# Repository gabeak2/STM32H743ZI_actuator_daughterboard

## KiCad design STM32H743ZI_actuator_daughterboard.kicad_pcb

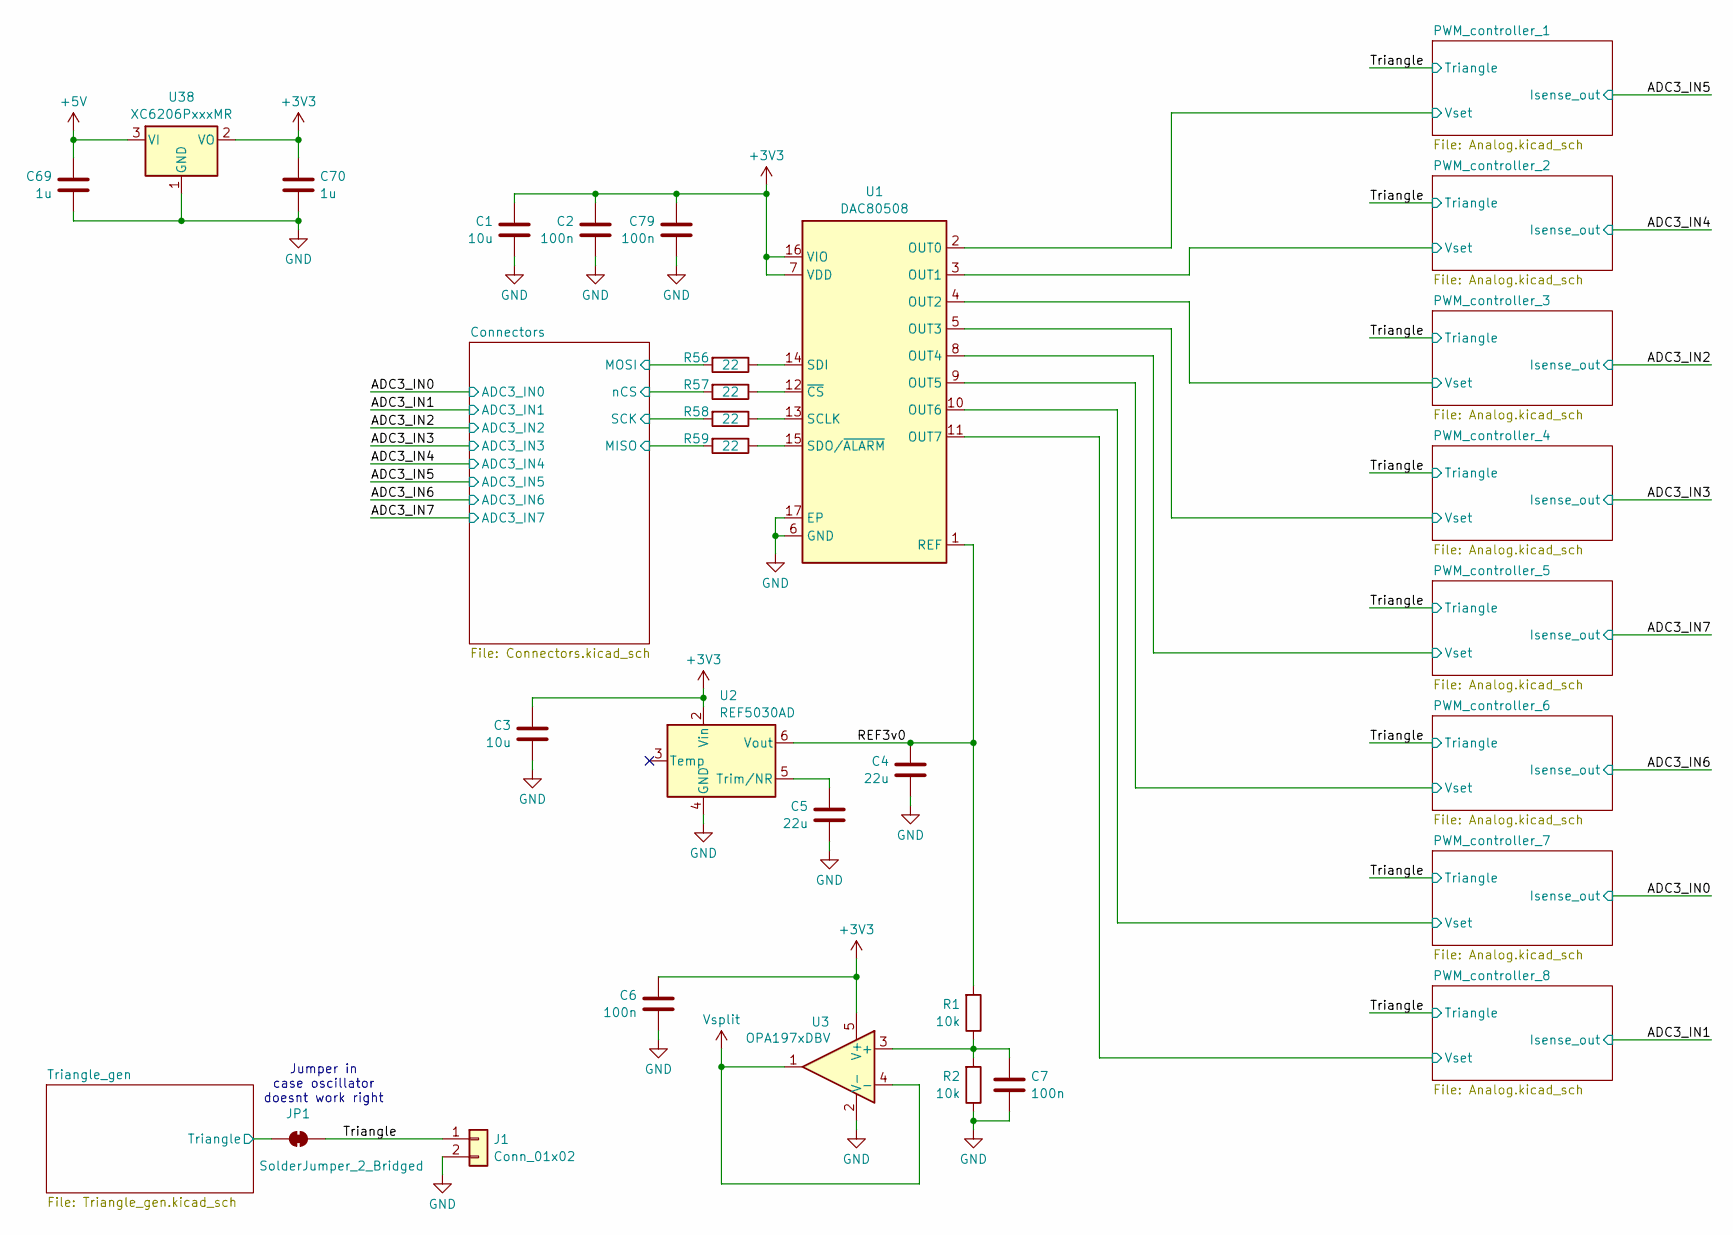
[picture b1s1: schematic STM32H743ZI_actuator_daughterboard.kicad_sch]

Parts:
C1, C3: 10u; C_0603_1608Metric; LCSC C19702
C2, C6, C7, C79: 100n; C_0603_1608Metric; LCSC C14663
C4, C5: 22u; C_0603_1608Metric; LCSC C59461
C69, C70: 1u; C_0603_1608Metric; LCSC C52923
J1: Conn_01x02; PinHeader_1x02_P2.54mm_Vertical
JP1: SolderJumper_2_Bridged; SolderJumper-2_P1.3mm_Bridged2Bar_Pad1.0x1.5mm
R1, R2: 10k; R_0603_1608Metric; LCSC C25804
R56, R57, R58, R59: 22; R_0603_1608Metric; LCSC C23345
U1: DAC80508; Texas_RTE0016D_WQFN-16-1EP_3x3mm_P0.5mm_EP0.8x0.8mm_Thermal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; LCSC C2679499
U2: REF5030AD; SOIC-8_3.9x4.9mm_P1.27mm; LCSC C69362
U3: OPA197xDBV; SOT-23-5; LCSC C221351
U38: XC6206PxxxMR; SOT-23-3; LCSC C5446

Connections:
+3V3: C1.1, C2.1, C3.1, C6.1, C70.1, C79.1, U1.7 (VDD), U1.16 (VIO), U2.2 (Vin), U3.5 (V+), U38.2 (VO); also elsewhere on the board
+5V: C69.1, U38.3 (VI); also elsewhere on the board
/Connectors/SPI1_MISO: R59.2; also elsewhere on the board
/Connectors/SPI1_MOSI: R56.2; also elsewhere on the board
/Connectors/SPI1_SCK: R58.2; also elsewhere on the board
/Connectors/SPI1_nCS: R57.2; also elsewhere on the board
/PWM_controller_1/Vset: U1.2 (OUT0); also elsewhere on the board
/PWM_controller_2/Vset: U1.3 (OUT1); also elsewhere on the board
/PWM_controller_3/Vset: U1.4 (OUT2); also elsewhere on the board
/PWM_controller_4/Vset: U1.5 (OUT3); also elsewhere on the board
/PWM_controller_5/Vset: U1.8 (OUT4); also elsewhere on the board
/PWM_controller_6/Vset: U1.9 (OUT5); also elsewhere on the board
/PWM_controller_7/Vset: U1.10 (OUT6); also elsewhere on the board
/PWM_controller_8/Vset: U1.11 (OUT7); also elsewhere on the board
/REF3v0: C4.1, R1.2, U1.1 (REF), U2.6 (Vout)
/Triangle: J1.1, JP1.1 (A); also elsewhere on the board
/Triangle_gen/Triangle: JP1.2 (B); also elsewhere on the board
GND: C1.2, C2.2, C3.2, C4.2, C5.2, C6.2, C7.2, C69.2, C70.2, C79.2, J1.2, R2.1, U1.6 (GND), U1.17 (EP), U2.4 (GND), U3.2 (V-), U38.1 (GND); also elsewhere on the board
unnamed: R58.1, U1.13 (SCLK)
unnamed: R56.1, U1.14 (SDI)
unnamed: R59.1, U1.15 (SDO/~ALARM)
unnamed: R57.1, U1.12 (~CS)
unnamed: C5.1, U2.5 (Trim/NR)
unnamed: C7.1, R1.1, R2.2, U3.3 (+)
Vsplit: U3.1, U3.4 (-); also elsewhere on the board

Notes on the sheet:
Jumper in case oscillator doesnt work right

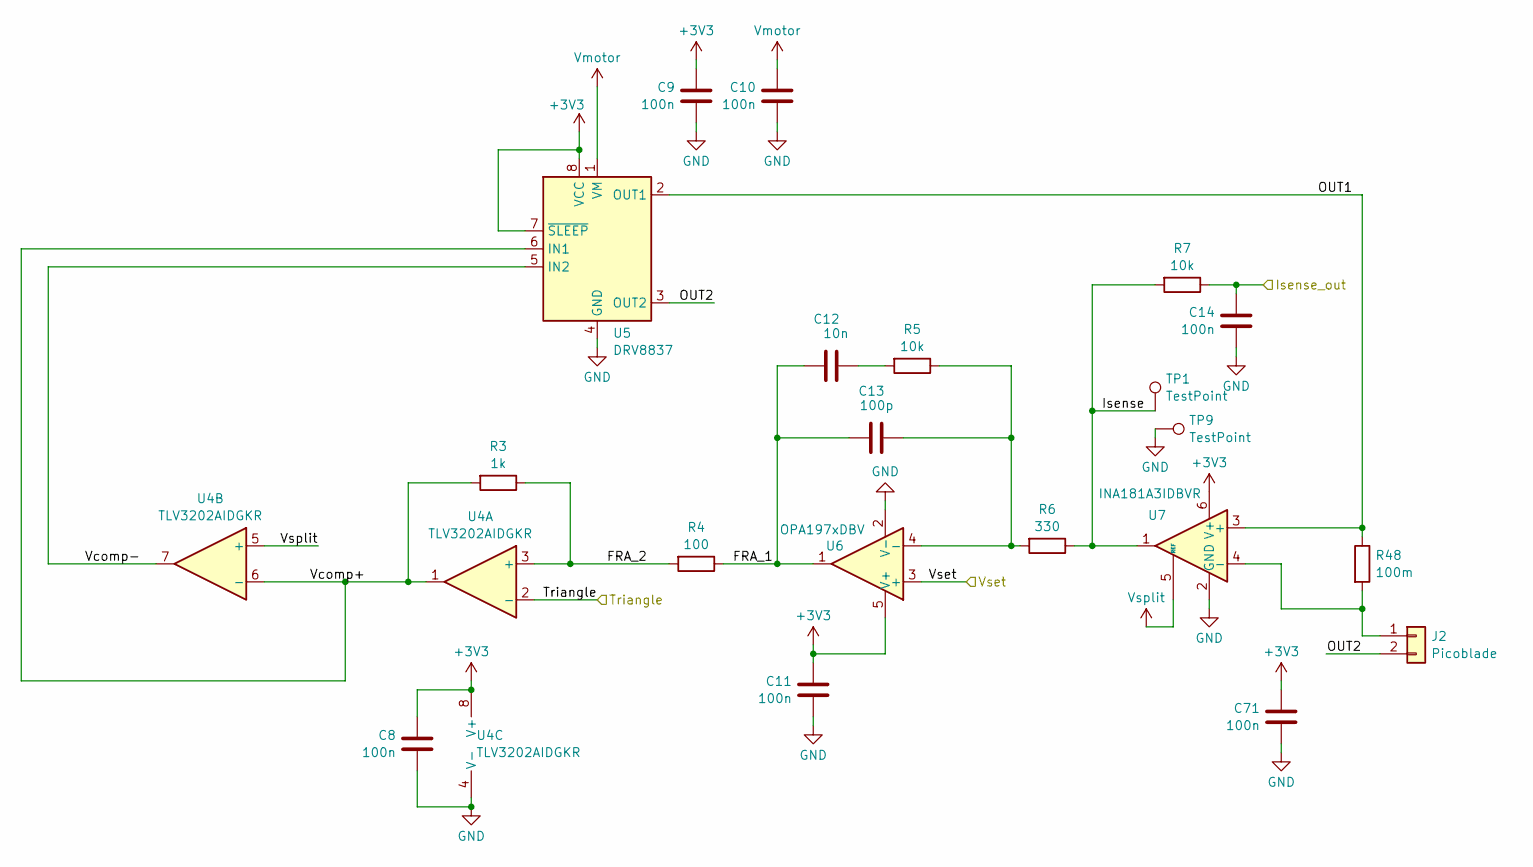
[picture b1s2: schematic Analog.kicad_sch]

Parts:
C8, C9, C10, C11, C14, C71: 100n; C_0603_1608Metric; LCSC C14663
C12: 10n; C_0603_1608Metric; LCSC C57112
C13: 100p; C_0603_1608Metric; LCSC C14858
J2: Picoblade; Molex_PicoBlade_53047-0210_1x02_P1.25mm_Vertical
R3: 1k; R_0603_1608Metric; LCSC C21190
R4: 100; R_0603_1608Metric; LCSC C22775
R5, R7: 10k; R_0603_1608Metric; LCSC C25804
R6: 330; R_0603_1608Metric; LCSC C23138
R48: 100m; R_1206_3216Metric; LCSC C25334
TP1, TP9: TestPoint; scope_tp
U4: TLV3202AIDGKR; VSSOP-8_3x3mm_P0.65mm; LCSC C478075
U5: DRV8837; WSON-8-1EP_2x2mm_P0.5mm_EP0.9x1.6mm; LCSC C39159
U6: OPA197xDBV; SOT-23-5; LCSC C221351
U7: INA181A3IDBVR; SOT-23-6; LCSC C2652255

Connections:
+3V3: C8.1, C9.1, C11.1, C71.1, U4.8 (V+), U5.7 (~SLEEP), U5.8 (VCC), U6.5 (V+), U7.6 (V+); also elsewhere on the board
/ADC3_IN5: C14.1, R7.1; also elsewhere on the board
/PWM_controller_1/FRA_1: C12.1, C13.1, R4.1, U6.1
/PWM_controller_1/FRA_2: R3.1, R4.2, U4.3 (+)
/PWM_controller_1/Isense: R6.1, R7.2, TP1.1 (1_1), U7.1
/PWM_controller_1/OUT1: R48.1, U5.2 (OUT1), U7.3 (+)
/PWM_controller_1/OUT2: J2.2, U5.3 (OUT2)
/PWM_controller_1/Vcomp+: R3.2, U4.1, U4.6 (-), U5.6 (IN1)
/PWM_controller_1/Vcomp-: U4.7, U5.5 (IN2)
/PWM_controller_1/Vset: U6.3 (+); also elsewhere on the board
/Triangle: U4.2 (-); also elsewhere on the board
GND: C8.2, C9.2, C10.2, C11.2, C14.2, C71.2, TP9.1 (1_1), U4.4 (V-), U5.4 (GND), U5.9 (GND), U6.2 (V-), U7.2 (GND); also elsewhere on the board
unnamed: C12.2, R5.2
unnamed: J2.1, R48.2, U7.4 (-)
unnamed: C13.2, R5.1, R6.2, U6.4 (-)
Vmotor: C10.1, U5.1 (VM); also elsewhere on the board
Vsplit: U4.5 (+), U7.5 (REF); also elsewhere on the board

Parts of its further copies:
C15, C16, C19, C20, C21, C22, C23, C26, C27, C28, C29, C30, C33, C34, C35, C36, C37, C40, C41, C42, C43, C44, C47, C48, C49, C50, C51, C54, C55, C56, C57, C58, C61, C62, C63, C72, C73, C74, C75, C76, C77, C78: 100n; C_0603_1608Metric; LCSC C14663
C17, C24, C31, C38, C45, C52, C59: 10n; C_0603_1608Metric; LCSC C57112
C18, C25, C32, C39, C46, C53, C60: 100p; C_0603_1608Metric; LCSC C14858
J5, J7, J9, J11, J13, J15, J17: Picoblade; Molex_PicoBlade_53047-0210_1x02_P1.25mm_Vertical
R8, R13, R18, R23, R28, R33, R38, R49, R50, R51, R52, R53, R54, R55: 10k; R_0603_1608Metric; LCSC C25804
R9, R14, R19, R24, R29, R34, R39: 1k; R_0603_1608Metric; LCSC C21190
R10, R15, R20, R25, R30, R35, R40: 330; R_0603_1608Metric; LCSC C23138
R11, R16, R21, R26, R31, R36, R41: 100; R_0603_1608Metric; LCSC C22775
R12, R17, R22, R27, R32, R37, R42: 100m; R_1206_3216Metric; LCSC C25334
TP2, TP3, TP4, TP5, TP6, TP7, TP8, TP10, TP11, TP12, TP13, TP14, TP15, TP16: TestPoint; scope_tp
U8, U12, U16, U20, U24, U28, U32: DRV8837; WSON-8-1EP_2x2mm_P0.5mm_EP0.9x1.6mm; LCSC C39159
U9, U13, U17, U21, U25, U29, U33: INA181A3IDBVR; SOT-23-6; LCSC C2652255
U10, U14, U18, U22, U26, U30, U34: TLV3202AIDGKR; VSSOP-8_3x3mm_P0.65mm; LCSC C478075
U11, U15, U19, U23, U27, U31, U35: OPA197xDBV; SOT-23-5; LCSC C221351

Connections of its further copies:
+3V3: C15.1, C19.1, C20.1, C21.1, C22.1, C26.1, C27.1, C28.1, C29.1, C33.1, C34.1, C35.1, C36.1, C40.1, C41.1, C42.1, C43.1, C47.1, C48.1, C49.1, C50.1, C54.1, C55.1, C56.1, C57.1, C61.1, C62.1, C63.1, U8.7 (~SLEEP), U8.8 (VCC), U9.6 (V+), U10.8 (V+), U11.5 (V+), U12.7 (~SLEEP), U12.8 (VCC), U13.6 (V+), U14.8 (V+), U15.5 (V+), U16.7 (~SLEEP), U16.8 (VCC), U17.6 (V+), U18.8 (V+), U19.5 (V+), U20.7 (~SLEEP), U20.8 (VCC), U21.6 (V+), U22.8 (V+), U23.5 (V+), U24.7 (~SLEEP), U24.8 (VCC), U25.6 (V+), U26.8 (V+), U27.5 (V+), U28.7 (~SLEEP), U28.8 (VCC), U29.6 (V+), U30.8 (V+), U31.5 (V+), U32.7 (~SLEEP), U32.8 (VCC), U33.6 (V+), U34.8 (V+), U35.5 (V+); also elsewhere on the board
/ADC3_IN0: C77.1, R54.1; also elsewhere on the board
/ADC3_IN1: C78.1, R55.1; also elsewhere on the board
/ADC3_IN2: C73.1, R50.1; also elsewhere on the board
/ADC3_IN3: C74.1, R51.1; also elsewhere on the board
/ADC3_IN4: C72.1, R49.1; also elsewhere on the board
/ADC3_IN6: C76.1, R53.1; also elsewhere on the board
/ADC3_IN7: C75.1, R52.1; also elsewhere on the board
/PWM_controller_2/FRA_1: C17.1, C18.1, R11.1, U11.1
/PWM_controller_2/FRA_2: R9.1, R11.2, U10.3 (+)
/PWM_controller_2/Isense: R10.1, R49.2, TP2.1 (1_1), U9.1
/PWM_controller_2/OUT1: R12.1, U8.2 (OUT1), U9.3 (+)
/PWM_controller_2/OUT2: J5.2, U8.3 (OUT2)
/PWM_controller_2/Vcomp+: R9.2, U8.6 (IN1), U10.1, U10.6 (-)
/PWM_controller_2/Vcomp-: U8.5 (IN2), U10.7
/PWM_controller_2/Vset: U11.3 (+); also elsewhere on the board
/PWM_controller_3/FRA_1: C24.1, C25.1, R16.1, U15.1
/PWM_controller_3/FRA_2: R14.1, R16.2, U14.3 (+)
/PWM_controller_3/Isense: R15.1, R50.2, TP3.1 (1_1), U13.1
/PWM_controller_3/OUT1: R17.1, U12.2 (OUT1), U13.3 (+)
/PWM_controller_3/OUT2: J7.2, U12.3 (OUT2)
/PWM_controller_3/Vcomp+: R14.2, U12.6 (IN1), U14.1, U14.6 (-)
/PWM_controller_3/Vcomp-: U12.5 (IN2), U14.7
/PWM_controller_3/Vset: U15.3 (+); also elsewhere on the board
/PWM_controller_4/FRA_1: C31.1, C32.1, R21.1, U19.1
/PWM_controller_4/FRA_2: R19.1, R21.2, U18.3 (+)
/PWM_controller_4/Isense: R20.1, R51.2, TP4.1 (1_1), U17.1
/PWM_controller_4/OUT1: R22.1, U16.2 (OUT1), U17.3 (+)
/PWM_controller_4/OUT2: J9.2, U16.3 (OUT2)
/PWM_controller_4/Vcomp+: R19.2, U16.6 (IN1), U18.1, U18.6 (-)
/PWM_controller_4/Vcomp-: U16.5 (IN2), U18.7
/PWM_controller_4/Vset: U19.3 (+); also elsewhere on the board
/PWM_controller_5/FRA_1: C38.1, C39.1, R26.1, U23.1
/PWM_controller_5/FRA_2: R24.1, R26.2, U22.3 (+)
/PWM_controller_5/Isense: R25.1, R52.2, TP5.1 (1_1), U21.1
/PWM_controller_5/OUT1: R27.1, U20.2 (OUT1), U21.3 (+)
/PWM_controller_5/OUT2: J11.2, U20.3 (OUT2)
/PWM_controller_5/Vcomp+: R24.2, U20.6 (IN1), U22.1, U22.6 (-)
/PWM_controller_5/Vcomp-: U20.5 (IN2), U22.7
/PWM_controller_5/Vset: U23.3 (+); also elsewhere on the board
/PWM_controller_6/FRA_1: C45.1, C46.1, R31.1, U27.1
/PWM_controller_6/FRA_2: R29.1, R31.2, U26.3 (+)
/PWM_controller_6/Isense: R30.1, R53.2, TP6.1 (1_1), U25.1
/PWM_controller_6/OUT1: R32.1, U24.2 (OUT1), U25.3 (+)
/PWM_controller_6/OUT2: J13.2, U24.3 (OUT2)
/PWM_controller_6/Vcomp+: R29.2, U24.6 (IN1), U26.1, U26.6 (-)
/PWM_controller_6/Vcomp-: U24.5 (IN2), U26.7
/PWM_controller_6/Vset: U27.3 (+); also elsewhere on the board
/PWM_controller_7/FRA_1: C52.1, C53.1, R36.1, U31.1
/PWM_controller_7/FRA_2: R34.1, R36.2, U30.3 (+)
/PWM_controller_7/Isense: R35.1, R54.2, TP7.1 (1_1), U29.1
/PWM_controller_7/OUT1: R37.1, U28.2 (OUT1), U29.3 (+)
/PWM_controller_7/OUT2: J15.2, U28.3 (OUT2)
/PWM_controller_7/Vcomp+: R34.2, U28.6 (IN1), U30.1, U30.6 (-)
/PWM_controller_7/Vcomp-: U28.5 (IN2), U30.7
/PWM_controller_7/Vset: U31.3 (+); also elsewhere on the board
/PWM_controller_8/FRA_1: C59.1, C60.1, R41.1, U35.1
/PWM_controller_8/FRA_2: R39.1, R41.2, U34.3 (+)
/PWM_controller_8/Isense: R40.1, R55.2, TP8.1 (1_1), U33.1
/PWM_controller_8/OUT1: R42.1, U32.2 (OUT1), U33.3 (+)
/PWM_controller_8/OUT2: J17.2, U32.3 (OUT2)
/PWM_controller_8/Vcomp+: R39.2, U32.6 (IN1), U34.1, U34.6 (-)
/PWM_controller_8/Vcomp-: U32.5 (IN2), U34.7
/PWM_controller_8/Vset: U35.3 (+); also elsewhere on the board
/Triangle: U10.2 (-), U14.2 (-), U18.2 (-), U22.2 (-), U26.2 (-), U30.2 (-), U34.2 (-); also elsewhere on the board
GND: C15.2, C16.2, C19.2, C20.2, C21.2, C22.2, C23.2, C26.2, C27.2, C28.2, C29.2, C30.2, C33.2, C34.2, C35.2, C36.2, C37.2, C40.2, C41.2, C42.2, C43.2, C44.2, C47.2, C48.2, C49.2, C50.2, C51.2, C54.2, C55.2, C56.2, C57.2, C58.2, C61.2, C62.2, C63.2, C72.2, C73.2, C74.2, C75.2, C76.2, C77.2, C78.2, TP10.1 (1_1), TP11.1 (1_1), TP12.1 (1_1), TP13.1 (1_1), TP14.1 (1_1), TP15.1 (1_1), TP16.1 (1_1), U8.4 (GND), U8.9 (GND), U9.2 (GND), U10.4 (V-), U11.2 (V-), U12.4 (GND), U12.9 (GND), U13.2 (GND), U14.4 (V-), U15.2 (V-), U16.4 (GND), U16.9 (GND), U17.2 (GND), U18.4 (V-), U19.2 (V-), U20.4 (GND), U20.9 (GND), U21.2 (GND), U22.4 (V-), U23.2 (V-), U24.4 (GND), U24.9 (GND), U25.2 (GND), U26.4 (V-), U27.2 (V-), U28.4 (GND), U28.9 (GND), U29.2 (GND), U30.4 (V-), U31.2 (V-), U32.4 (GND), U32.9 (GND), U33.2 (GND), U34.4 (V-), U35.2 (V-); also elsewhere on the board
unnamed: C17.2, R8.2
unnamed: C24.2, R13.2
unnamed: C31.2, R18.2
unnamed: C38.2, R23.2
unnamed: C45.2, R28.2
unnamed: C52.2, R33.2
unnamed: C59.2, R38.2
unnamed: J5.1, R12.2, U9.4 (-)
unnamed: J7.1, R17.2, U13.4 (-)
unnamed: J9.1, R22.2, U17.4 (-)
unnamed: J11.1, R27.2, U21.4 (-)
unnamed: J13.1, R32.2, U25.4 (-)
unnamed: J15.1, R37.2, U29.4 (-)
unnamed: J17.1, R42.2, U33.4 (-)
unnamed: C18.2, R8.1, R10.2, U11.4 (-)
unnamed: C25.2, R13.1, R15.2, U15.4 (-)
unnamed: C32.2, R18.1, R20.2, U19.4 (-)
unnamed: C39.2, R23.1, R25.2, U23.4 (-)
unnamed: C46.2, R28.1, R30.2, U27.4 (-)
unnamed: C53.2, R33.1, R35.2, U31.4 (-)
unnamed: C60.2, R38.1, R40.2, U35.4 (-)
Vmotor: C16.1, C23.1, C30.1, C37.1, C44.1, C51.1, C58.1, U8.1 (VM), U12.1 (VM), U16.1 (VM), U20.1 (VM), U24.1 (VM), U28.1 (VM), U32.1 (VM); also elsewhere on the board
Vsplit: U9.5 (REF), U10.5 (+), U13.5 (REF), U14.5 (+), U17.5 (REF), U18.5 (+), U21.5 (REF), U22.5 (+), U25.5 (REF), U26.5 (+), U29.5 (REF), U30.5 (+), U33.5 (REF), U34.5 (+); also elsewhere on the board

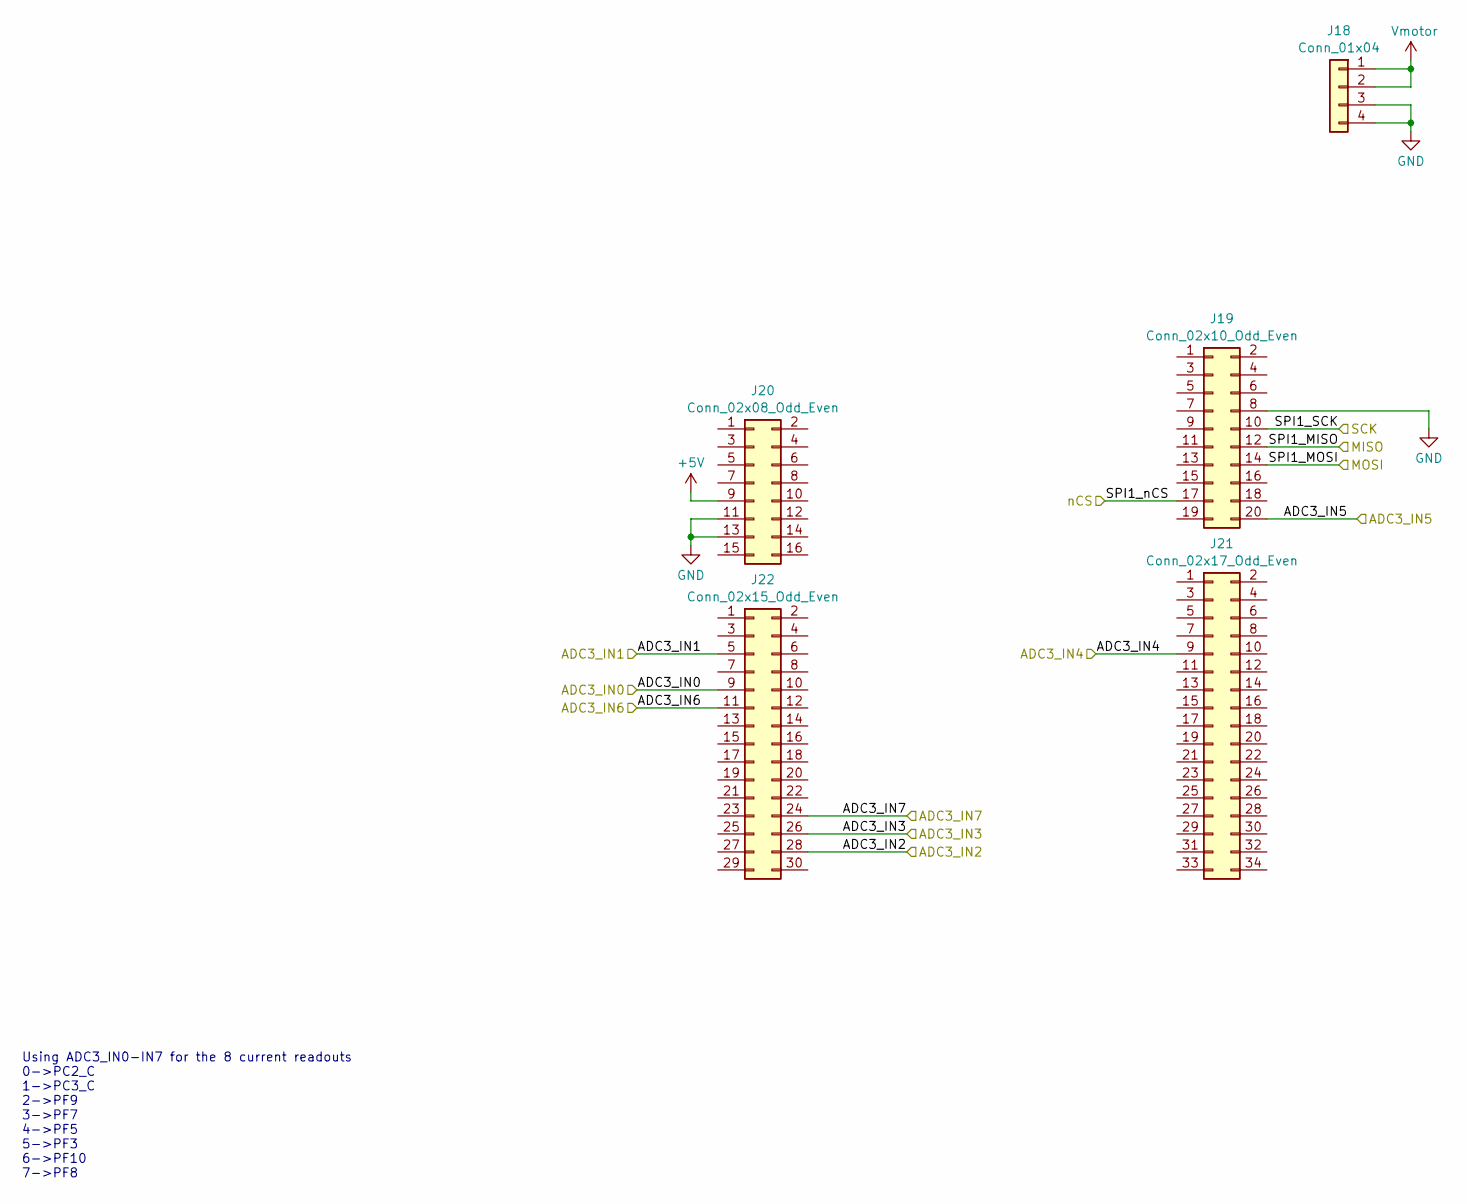
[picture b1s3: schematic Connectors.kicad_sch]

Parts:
J18: Conn_01x04; PinHeader_1x04_P2.54mm_Vertical
J19: Conn_02x10_Odd_Even; PinHeader_2x10_P2.54mm_Vertical
J20: Conn_02x08_Odd_Even; PinHeader_2x08_P2.54mm_Vertical
J21: Conn_02x17_Odd_Even; PinHeader_2x17_P2.54mm_Vertical
J22: Conn_02x15_Odd_Even; PinHeader_2x15_P2.54mm_Vertical

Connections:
+5V: J20.9; also elsewhere on the board
/ADC3_IN0: J22.9; also elsewhere on the board
/ADC3_IN1: J22.5; also elsewhere on the board
/ADC3_IN2: J22.28; also elsewhere on the board
/ADC3_IN3: J22.26; also elsewhere on the board
/ADC3_IN4: J21.9 (Pin_9_9); also elsewhere on the board
/ADC3_IN5: J19.20; also elsewhere on the board
/ADC3_IN6: J22.11; also elsewhere on the board
/ADC3_IN7: J22.24; also elsewhere on the board
/Connectors/SPI1_MISO: J19.12; also elsewhere on the board
/Connectors/SPI1_MOSI: J19.14; also elsewhere on the board
/Connectors/SPI1_SCK: J19.10; also elsewhere on the board
/Connectors/SPI1_nCS: J19.17; also elsewhere on the board
GND: J18.3, J18.4, J19.8, J20.11, J20.13; also elsewhere on the board
Vmotor: J18.1, J18.2; also elsewhere on the board

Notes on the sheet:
Using ADC3_IN0-IN7 for the 8 current readouts 0->PC2_C 1->PC3_C 2->PF9 3->PF7 4->PF5 5->PF3 6->PF10 7->PF8

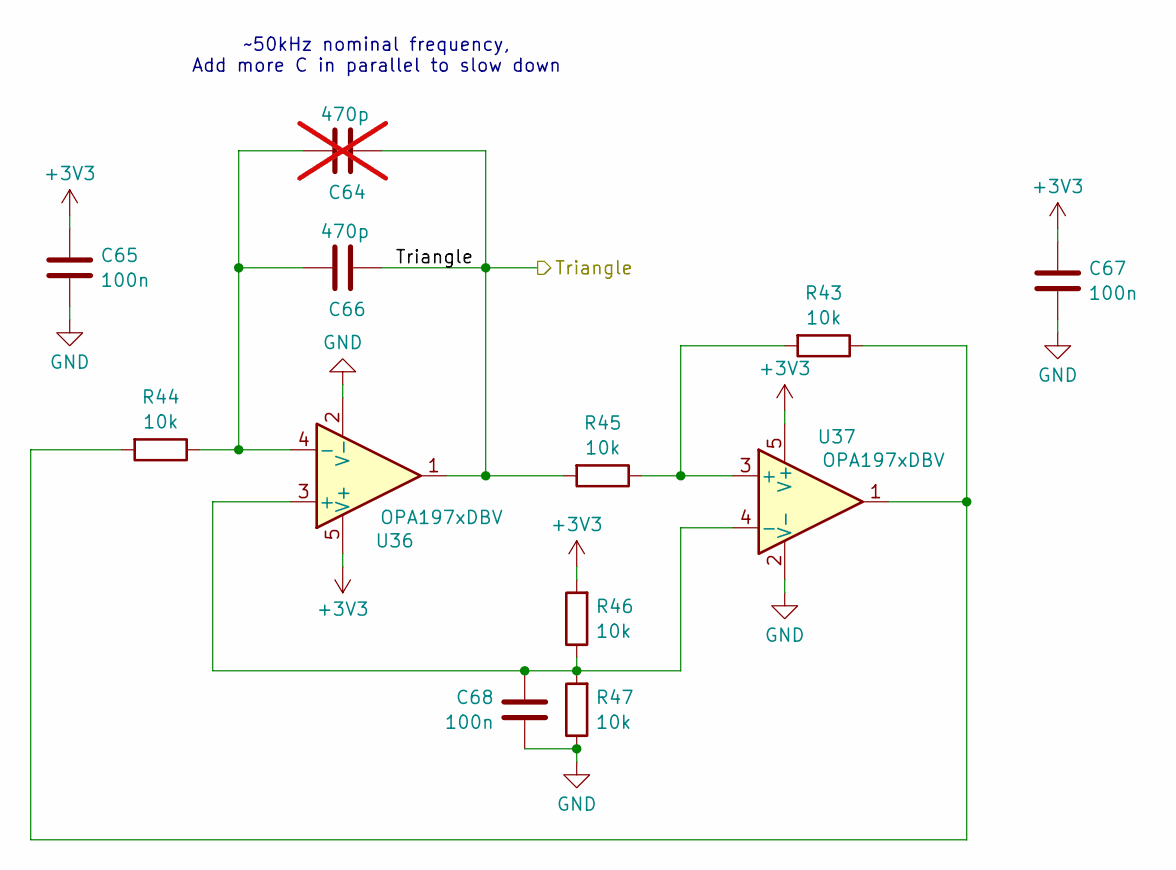
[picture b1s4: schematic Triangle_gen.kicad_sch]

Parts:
C64: 470p; C_0603_1608Metric; LCSC C1620; not fitted
C65, C67, C68: 100n; C_0603_1608Metric; LCSC C14663
C66: 470p; C_0603_1608Metric; LCSC C1620
R43, R44, R45, R46, R47: 10k; R_0603_1608Metric; LCSC C25804
U36, U37: OPA197xDBV; SOT-23-5; LCSC C221351

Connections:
+3V3: C65.1, C67.1, R46.2, U36.5 (V+), U37.5 (V+); also elsewhere on the board
/Triangle_gen/Triangle: C64.1, C66.1, R45.2, U36.1; also elsewhere on the board
GND: C65.2, C67.2, C68.2, R47.1, U36.2 (V-), U37.2 (V-); also elsewhere on the board
unnamed: R43.1, R44.2, U37.1
unnamed: C68.1, R46.1, R47.2, U36.3 (+), U37.4 (-)
unnamed: C64.2, C66.2, R44.1, U36.4 (-)
unnamed: R43.2, R45.1, U37.3 (+)

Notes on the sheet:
~50kHz nominal frequency, Add more C in parallel to slow down

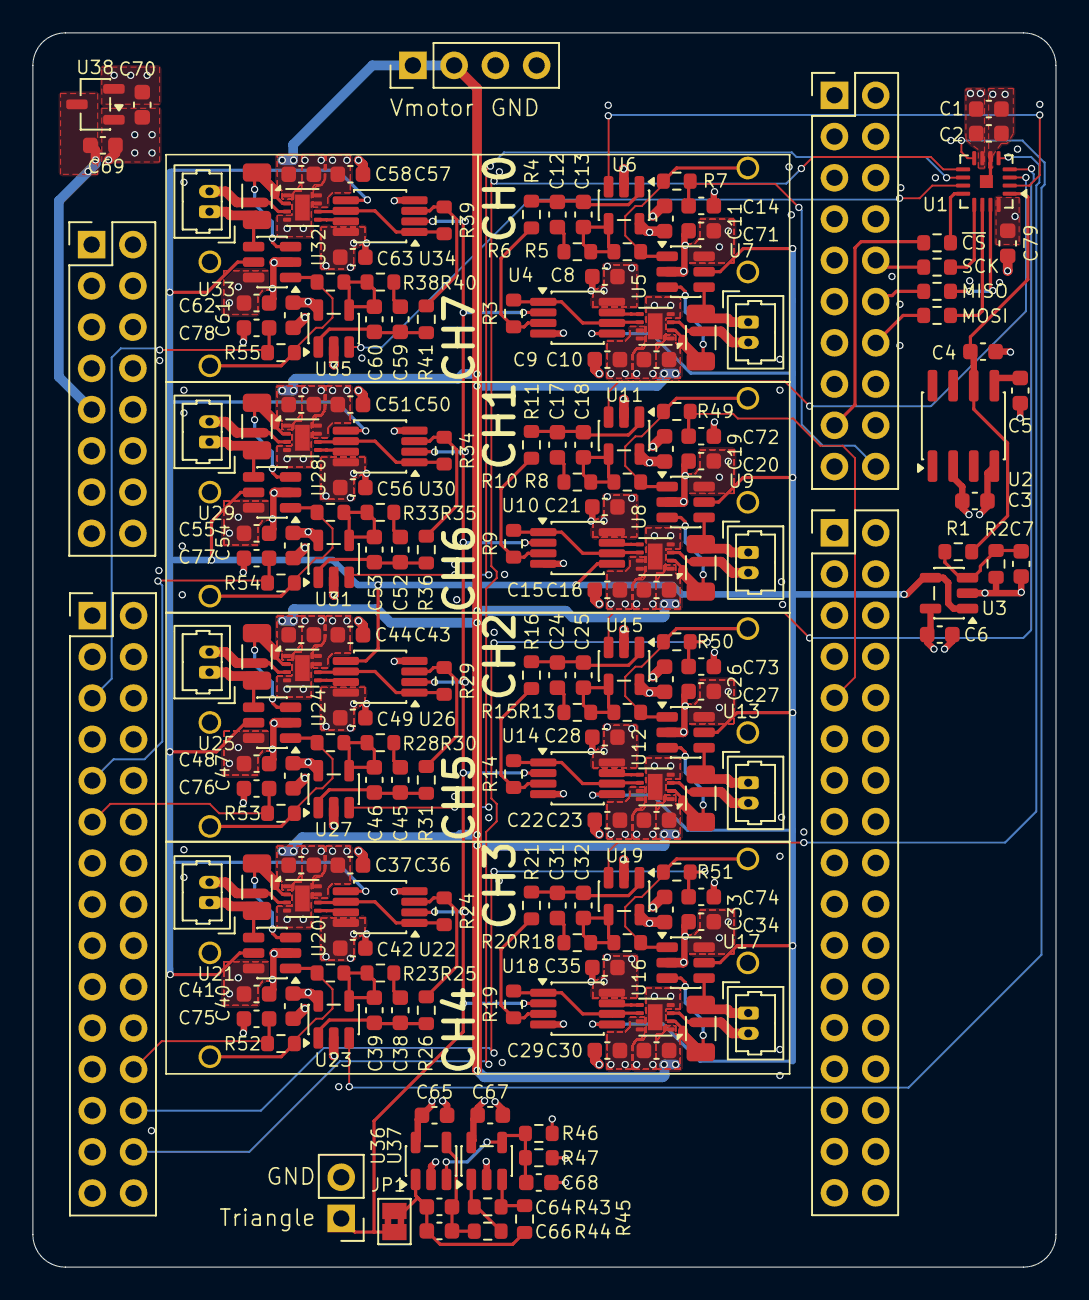
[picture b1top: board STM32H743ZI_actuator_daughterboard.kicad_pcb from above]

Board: 4 copper layers, 63.0 x 76.0 mm, 207 parts (0 on the bottom side), 118 nets.

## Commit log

2026-03-28 8ch layout applied, connectors aligned to nucleo
2026-03-28 Working on how to arrange 8 channels
2026-04-04 Continuing layout, added ADC connections for current measurements
2026-04-05 Basically Done with Layout, final checks and let it sit a day before ordering
